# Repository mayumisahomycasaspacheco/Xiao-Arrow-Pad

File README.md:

# Xiao Arrow Pad

A 5-key macropad designed in KiCad and Fusion 360 using a Seeed XIAO RP2040.

Why I made the Hackpad?
I really wanted to take on this challenge; I'd never done a hardware project before, so the idea really excited me. Although I've had to modify my project several times, I think it's been worth it, since I've learned a lot from my mistakes. I hope to continue challenging myself even more.

## Schematic

## PCB

## Case

## Firmware
This project uses KMK firmware.

## BOM

- 5x Cherry MX Switches
- 2x SK6812 MINI LEDs
- 1x Seeed XIAO RP2040 DIP
- 5x Blank DSA Keycaps
- 4x M3x8 Bolt
- 4x M2x5 Socket Head Cap Screw
- PCB (2 layers)

### DRC Note

KiCad reports a board edge clearance warning near the LED cutout.This is caused by the LED footprint pads being very close to the cutout. The cutout is intentional and the warning was reviewed and accepted.

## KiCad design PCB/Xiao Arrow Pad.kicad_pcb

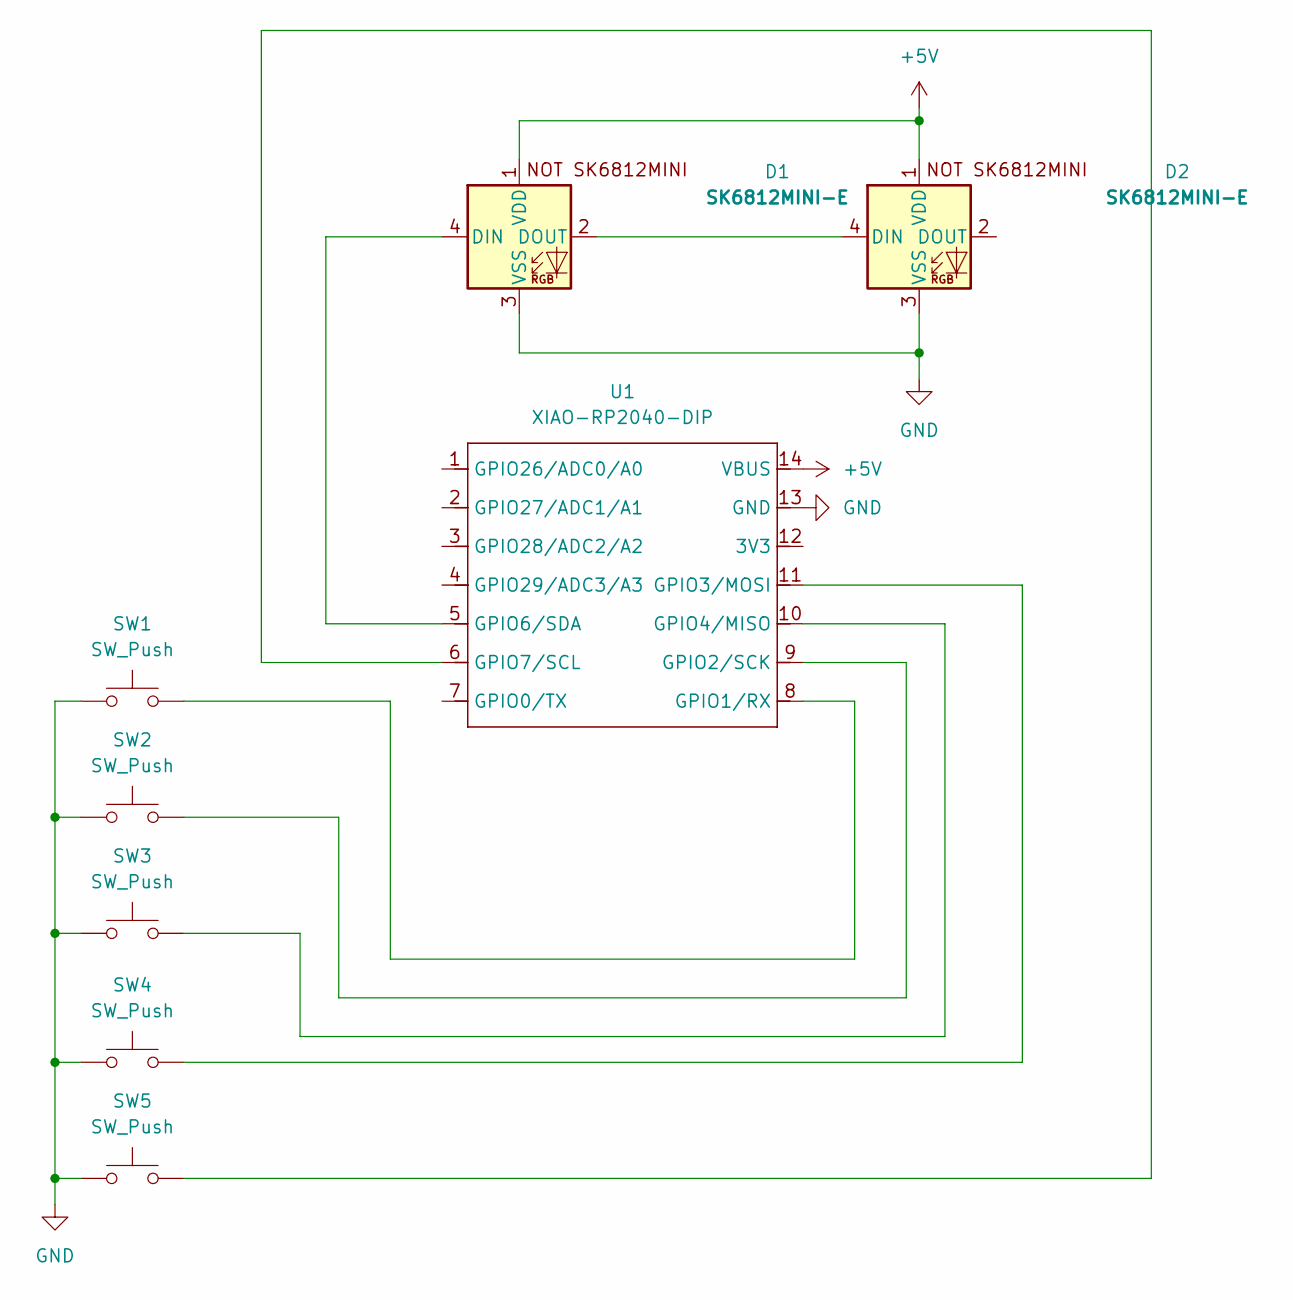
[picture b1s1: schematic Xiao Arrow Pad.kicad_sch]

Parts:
D1, D2: SK6812MINI-E; MX_SK6812MINI-E_REV
SW1, SW2, SW3, SW4, SW5: SW_Push; SW_Cherry_MX_1.00u_PCB
U1: XIAO-RP2040-DIP

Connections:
+5V: D1.1 (VDD), D2.1 (VDD), U1.14 (VBUS)
GND: D1.3 (VSS), D2.3 (VSS), SW1.1, SW2.1, SW3.1, SW4.1, SW5.1, U1.13 (GND)
unnamed: D1.4 (DIN), U1.5 (GPIO6/SDA)
unnamed: D1.2 (DOUT), D2.4 (DIN)
unnamed: SW1.2, U1.8 (GPIO1/RX)
unnamed: SW2.2, U1.9 (GPIO2/SCK)
unnamed: SW4.2, U1.11 (GPIO3/MOSI)
unnamed: SW3.2, U1.10 (GPIO4/MISO)
unnamed: SW5.2, U1.6 (GPIO7/SCL)

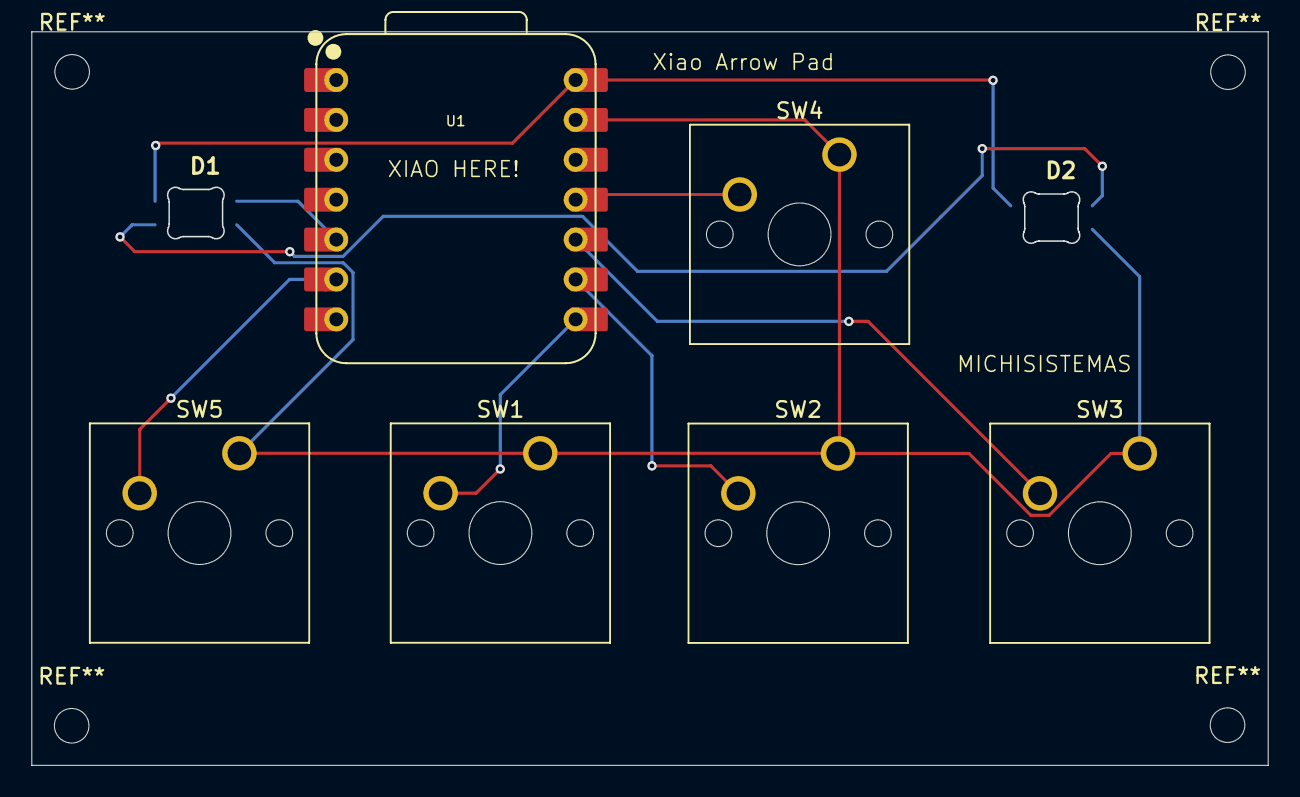
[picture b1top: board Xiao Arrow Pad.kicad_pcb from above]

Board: 2 copper layers, 78.7 x 46.7 mm, 8 parts (0 on the bottom side), 9 nets.

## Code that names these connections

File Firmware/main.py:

# Hello, I'm michisistemas, here I'll be making the firmware for Miauyummi's First Project

import board
from kmk.kmk_keyboard import KMKKeyboard
from kmk.scanners.keypad import KeysScanner
from kmk.keys import KC

keyboard = KMKKeyboard()

# EXACT pins according to my KiCad schematic

PINS = [
    board.GP1,  # SW1 → GPIO1 → Izquierda
    board.GP2,  # SW2 → GPIO2 → Abajo
    board.GP4,  # SW3 → GPIO4 → Derecha
    board.GP3,  # SW4 → GPIO3 → Arriba
    board.GP7,  # SW5 → GPIO7 → Espacio
]

keyboard.matrix = KeysScanner(
    pins=PINS,
    value_when_pressed=False,
)

keyboard.keymap = [[
    KC.LEFT,   # SW1
    KC.DOWN,   # SW2
    KC.RIGHT,  # SW3
    KC.UP,     # SW4
    KC.SPACE,  # SW5
]]

keyboard.go()

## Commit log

2026-01-27 Primer commit
